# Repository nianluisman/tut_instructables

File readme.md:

# Build Custom ESP32 Boards From Scratch! 
This project is based on a online tutorial that I did not make. I build this just for fun and to learn something about kicad.

https://www.instructables.com/Build-Custom-ESP32-Boards-From-Scratch-the-Complet/

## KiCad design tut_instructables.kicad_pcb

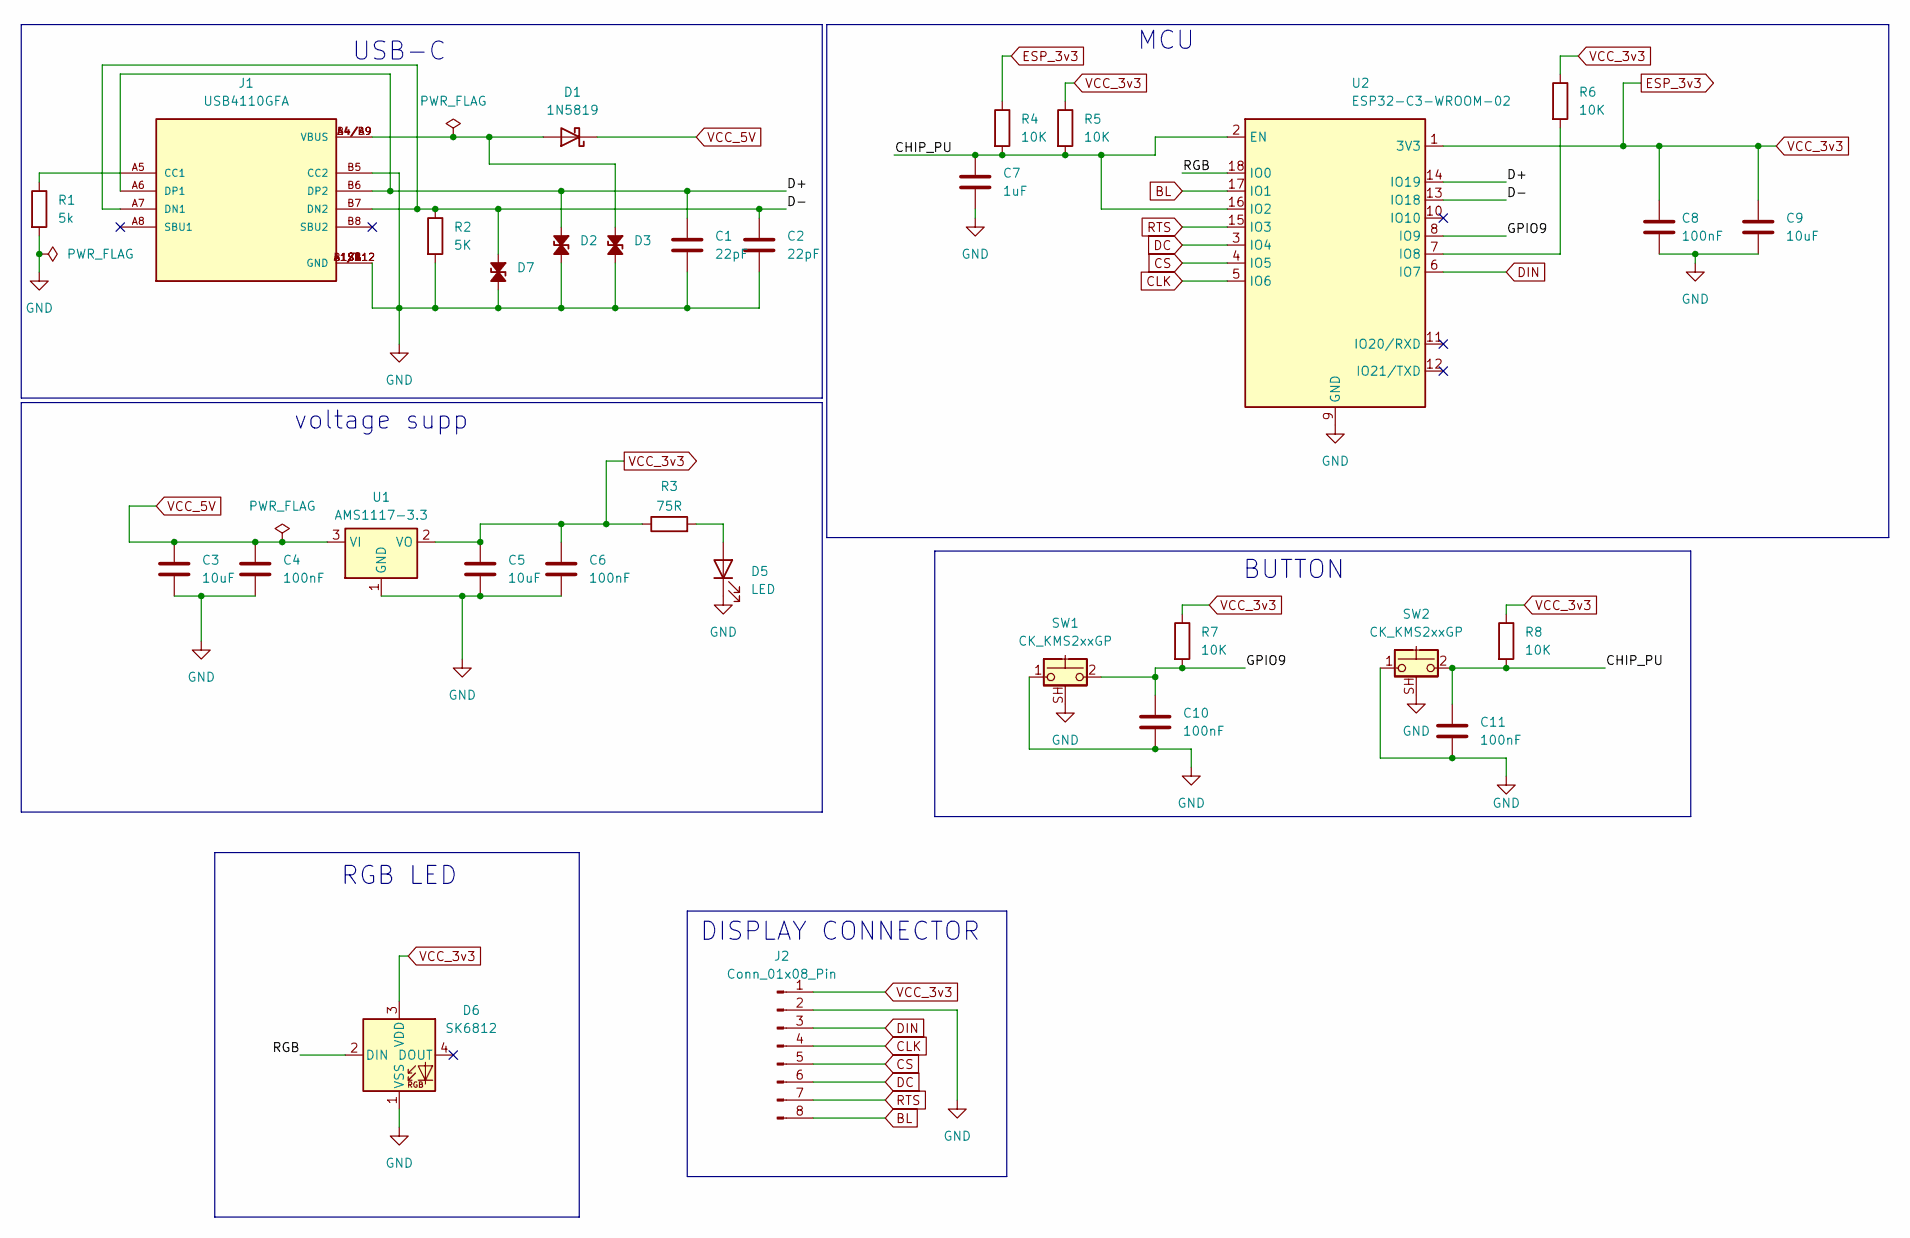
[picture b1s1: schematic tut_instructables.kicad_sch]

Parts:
C1, C2: 22pF; C_0201_0603Metric
C3, C5, C9: 10uF; C_0201_0603Metric
C4, C6, C8, C10, C11: 100nF; C_0201_0603Metric
C7: 1uF; C_0201_0603Metric
D1: 1N5819; D_0201_0603Metric
D2, D3, D7: D_0201_0603Metric
D5: LED; LED_0201_0603Metric
D6: SK6812; LED_SK6812_PLCC4_5.0x5.0mm_P3.2mm
J1: USB4110GFA; GCT_USB4110GFA
J2: Conn_01x08_Pin; PinHeader_1x08_P2.00mm_Vertical
R1: 5k; R_0201_0603Metric
R2: 5K; R_0201_0603Metric
R3: 75R; R_0201_0603Metric
R4, R5, R6, R7, R8: 10K; R_0201_0603Metric
SW1, SW2: CK_KMS2xxGP; SW_SPST_CK_KMS2xxGP
U1: AMS1117-3.3; SOT-223-3_TabPin2
U2: ESP32-C3-WROOM-02

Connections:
/CHIP_PU: C7.1, C11.1, R4.2, R5.2, R8.2, SW2.2, U2.2 (EN), U2.16 (IO2)
/D+: C1.1, D2.1 (A1), J1.A6 (DP1), J1.B6 (DP2), U2.14 (IO19)
/D-: C2.1, D7.1 (A1), J1.A7 (DN1), J1.B7 (DN2), R2.1, U2.13 (IO18)
/GPIO9: C10.1, R7.2, SW1.2, U2.8 (IO9)
/RGB: D6.2 (DIN), U2.18 (IO0)
BL: J2.8, U2.17 (IO1)
CLK: J2.4, U2.5 (IO6)
CS: J2.5, U2.4 (IO5)
DC: J2.6, U2.3 (IO4)
DIN: J2.3, U2.6 (IO7)
ESP_3v3: C5.1, C6.1, C8.1, C9.1, D6.3 (VDD), J2.1, R3.1, R4.1, R5.1, R6.1, R7.1, R8.1, U1.2 (VO), U2.1 (3V3)
GND: C1.2, C2.2, C3.2, C4.2, C5.2, C6.2, C7.2, C8.2, C9.2, C10.2, C11.2, D2.2 (A2), D3.2 (A2), D5.1 (K), D6.1 (VSS), D7.2 (A2), J1.A1/B12 (GND), J1.B1/A12 (GND), J1.B5 (CC2), J1.S1 (GND), J1.S2 (GND), J1.S3 (GND), J1.S4 (GND), J2.2, R1.2, R2.2, SW1.1, SW1.SH (B), SW2.1, SW2.SH (B), U1.1 (GND), U2.9 (GND), U2.19 (GND)
unnamed: D1.2 (A), D3.1 (A1), J1.A4/B9 (VBUS), J1.B4/A9 (VBUS)
unnamed: D5.2 (A), R3.2
unnamed: J1.A5 (CC1), R1.1
unnamed: R6.2, U2.7 (IO8)
RTS: J2.7, U2.15 (IO3)
VCC_5V: C3.1, C4.1, D1.1 (K), U1.3 (VI)

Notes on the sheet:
voltage supp
USB-C
MCU
RGB LED
BUTTON
DISPLAY CONNECTOR

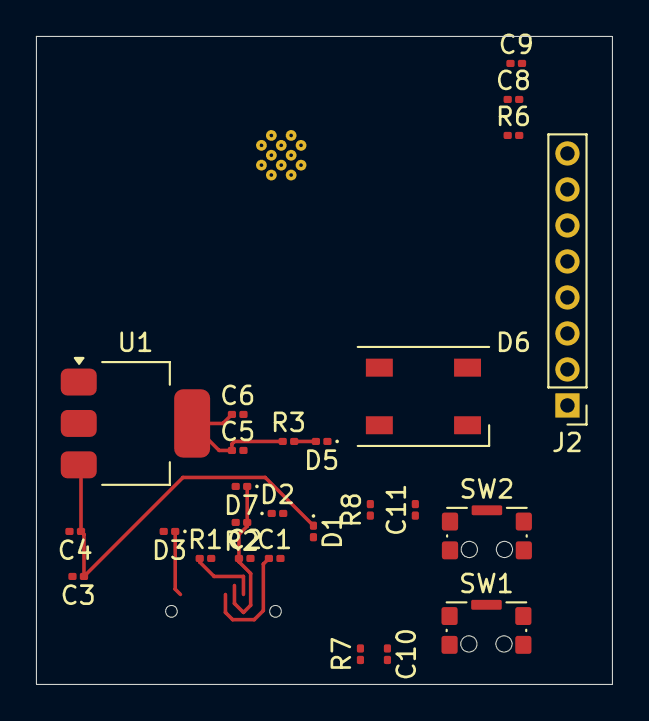
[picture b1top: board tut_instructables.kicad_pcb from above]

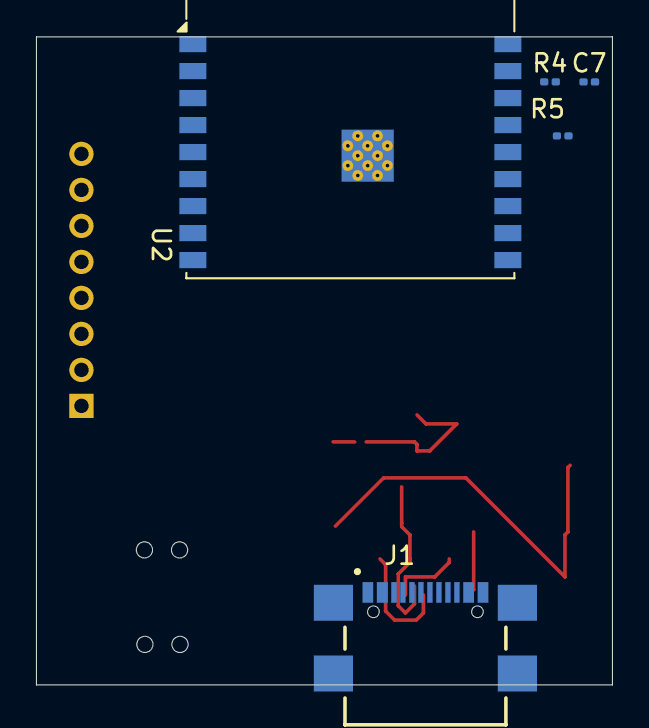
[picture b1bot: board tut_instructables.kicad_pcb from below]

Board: 2 copper layers, 32.0 x 36.0 mm, 31 parts (5 on the bottom side), 18 nets.

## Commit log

2025-03-20 init project
2025-03-20 add readme
2025-03-21 added all the footprints
2025-03-23 stated routing the pcb
